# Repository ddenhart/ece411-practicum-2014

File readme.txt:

// ECE 411 - readme
// ddenhart@pdx.edu
// jerscott@pdx.edu
// ccarmen@pdx.edu
// nsl2@pdx.edu

---2014.10.05 nslj---
   - Initial readme added
   - Added Carmen's decision matrix to repo
   - Added Carmen's project proposals to repo
   - Added Jeremiah's project proposals to repo
   - Added Nick's project proposals to repo
   - Added Deb's project proposals to repo
   - Added personal scoring to decision matrix
  
---2014.10.05 dd---
   - Added personal scoring to decision matrix
   - updated readme 

---2014.10.06 ccarmen---
   - Added personal scoring to decision matrix
   - Added approx. cost for my proposals
   - updated readme 

---2014.10.06 jerscott---
   - Added scores and proposal costs to decision matrix
   - updated readme

---2014.10.08 nslj---
   - Added theoretical block diagram for belt project   

---2014.10.09 ccarmen---
   - Added meeting minutes on Wiki 
   - Added decision matrix 
 
---2014.10.11 dd---
   - Added color sensing proposals

---2014.10.11 jerscott---
   - Added power and vague proposals

---2014.10.11 nslj---
   - Added system overview block diagram
   - New stage folder created

---2014.10.11 ccarmen—--
   - Added LED options powerpoint

---2014.10.12 nslj---
   - Reorganized file folders to reflect latest updates (for observers)
   - Added the alternate proposals write up for HW2

---2014.10.12 jerscott---
   - Added updated Practicum Proposal

---2014.10.14 dd---
   -Added musts, shoulds and mays to the logbook wiki
   -Added datasheets & product links to the wiki
   -Filled out class forms with team members and project name
   -Added Microcontroller and Color Sensor datasheets and purchasing links to wiki
   -Added In-System Programmer links to wiki

---2014.10.14 ccarmen---
   - Added 10/11/2014 meeting minutes
   - Added RGB LED strip datasheet & product link to the wiki

---2014.10.16 ccarmen---
   - Added AVR programmer option links on Datasheet & Product Links page

---2014.10.18 ccarmen---
   - Added 10/18/2014 meeting minutes on the Wiki

---2014.10.18 dd---
   -Updated Wiki to have the T10 name and added summary
   -Added Project Proposal and Decision Matrix Pages
   -Made organized Wiki sidebar

---2014.10.19 cc---
   -Added LED output drawing to provide info for the project schematic

---2014.10.20 dd---
   - Added Color Sensor block drawing
   
---2014.10.21 cc---
   - Carmen Ciobanu implemented the new Weekly Progress Report format on the Wiki (individual and team combined)

---2014.10.22 dd---
   -Added the template pages for the individual weekly reports on the wiki
   -Filled in the past weekly reports

---2014.10.23 dd---
  - installed avr studio to start learning
  - installed winavr to start learning

---2014.10.23 jerscott---
   - Added PDS
   
---2014.10.24 dd---
   - Color sensors, Micontrollers, test RGB leds, power supply and ISP parts arrived

---2014.10.24 nslj---
   - Added schematic rough draft
   - Added brief write up on adding custom libraries to EAGLE

---2014.10.24 nslj---
  - Added meeting minues and updated WPR

---2014.10.27 jerscott---
   - Uploaded Revision 2 PDS

---2014.10.27 dd---
   - Sync'd readme and wpr's
   - breadboard power adapter component and last of other connectors arrived

---2014.10.29 nslj---
   - Added preliminary schematic for turn in
   - Updated wiki with schematic info
 
---2014.11.02 dd---
   - Sync'd readme and wpr's

---2014.11.5 nslj---
   - preliminary board layout uploaded
   - updated wiki with layout info

---2014.11.6 nslj---
   - completely rerouted board with correct size traces
   - redid components based on preliminary bill of materials
   - new switch, new capacitors!

---2014.11.06 jerscott---
   - Provided feedback for project schematic and board layout

---2014.11.07 cc---
   - Provided feedback for project schematic and board layout
   - Identified all the parts needed for our board on Digi-Key website and found new parts for the "package not available or not in stock" case
   - Created BOM with extra fields for manufacturer name, manufacturer part number, Digi-Key part number and direct links to components on Digi-Key website
   - Ordered all components on the BOM
   
---2014.11.08 dd---
   - made part names readable on the board 
   - project schedule proposal

---2014.11.08 cc—--
   - Received all board components from Digi-key
   - Printed board layout and put components on top
   - Good match 
   - Finished editing final version of BOM document

---2014.11.08 nslj---
   - final layout candidate uploaded!
     --fixed airwire @ (1.30,1.05)
     --smashed/sized some test points in Schematic
     --updated dimension layer of board for better spacing of mounting holes
     --added teamname info to both tPlace and tSilk layers
     --png screenshots of final layout candidate?

---2014.11.09 cc—--
   - Created Project Schedule document from project schedule documents provided by each team member
  
---2014.11.10 dd---
   - Reviewed and fitted the Project Schedule
   
---2014.11.15 dd---
   - Added the color sensor uml activity view

---2014.11.15 cc—--
   - Added LED Output driver protocol sequence diagram

---2014.11.16 nslj---
   - Added L0 system view block diagram
   - Added L1 system view block diagram
   - Added L0 module view for subcomponents in system view

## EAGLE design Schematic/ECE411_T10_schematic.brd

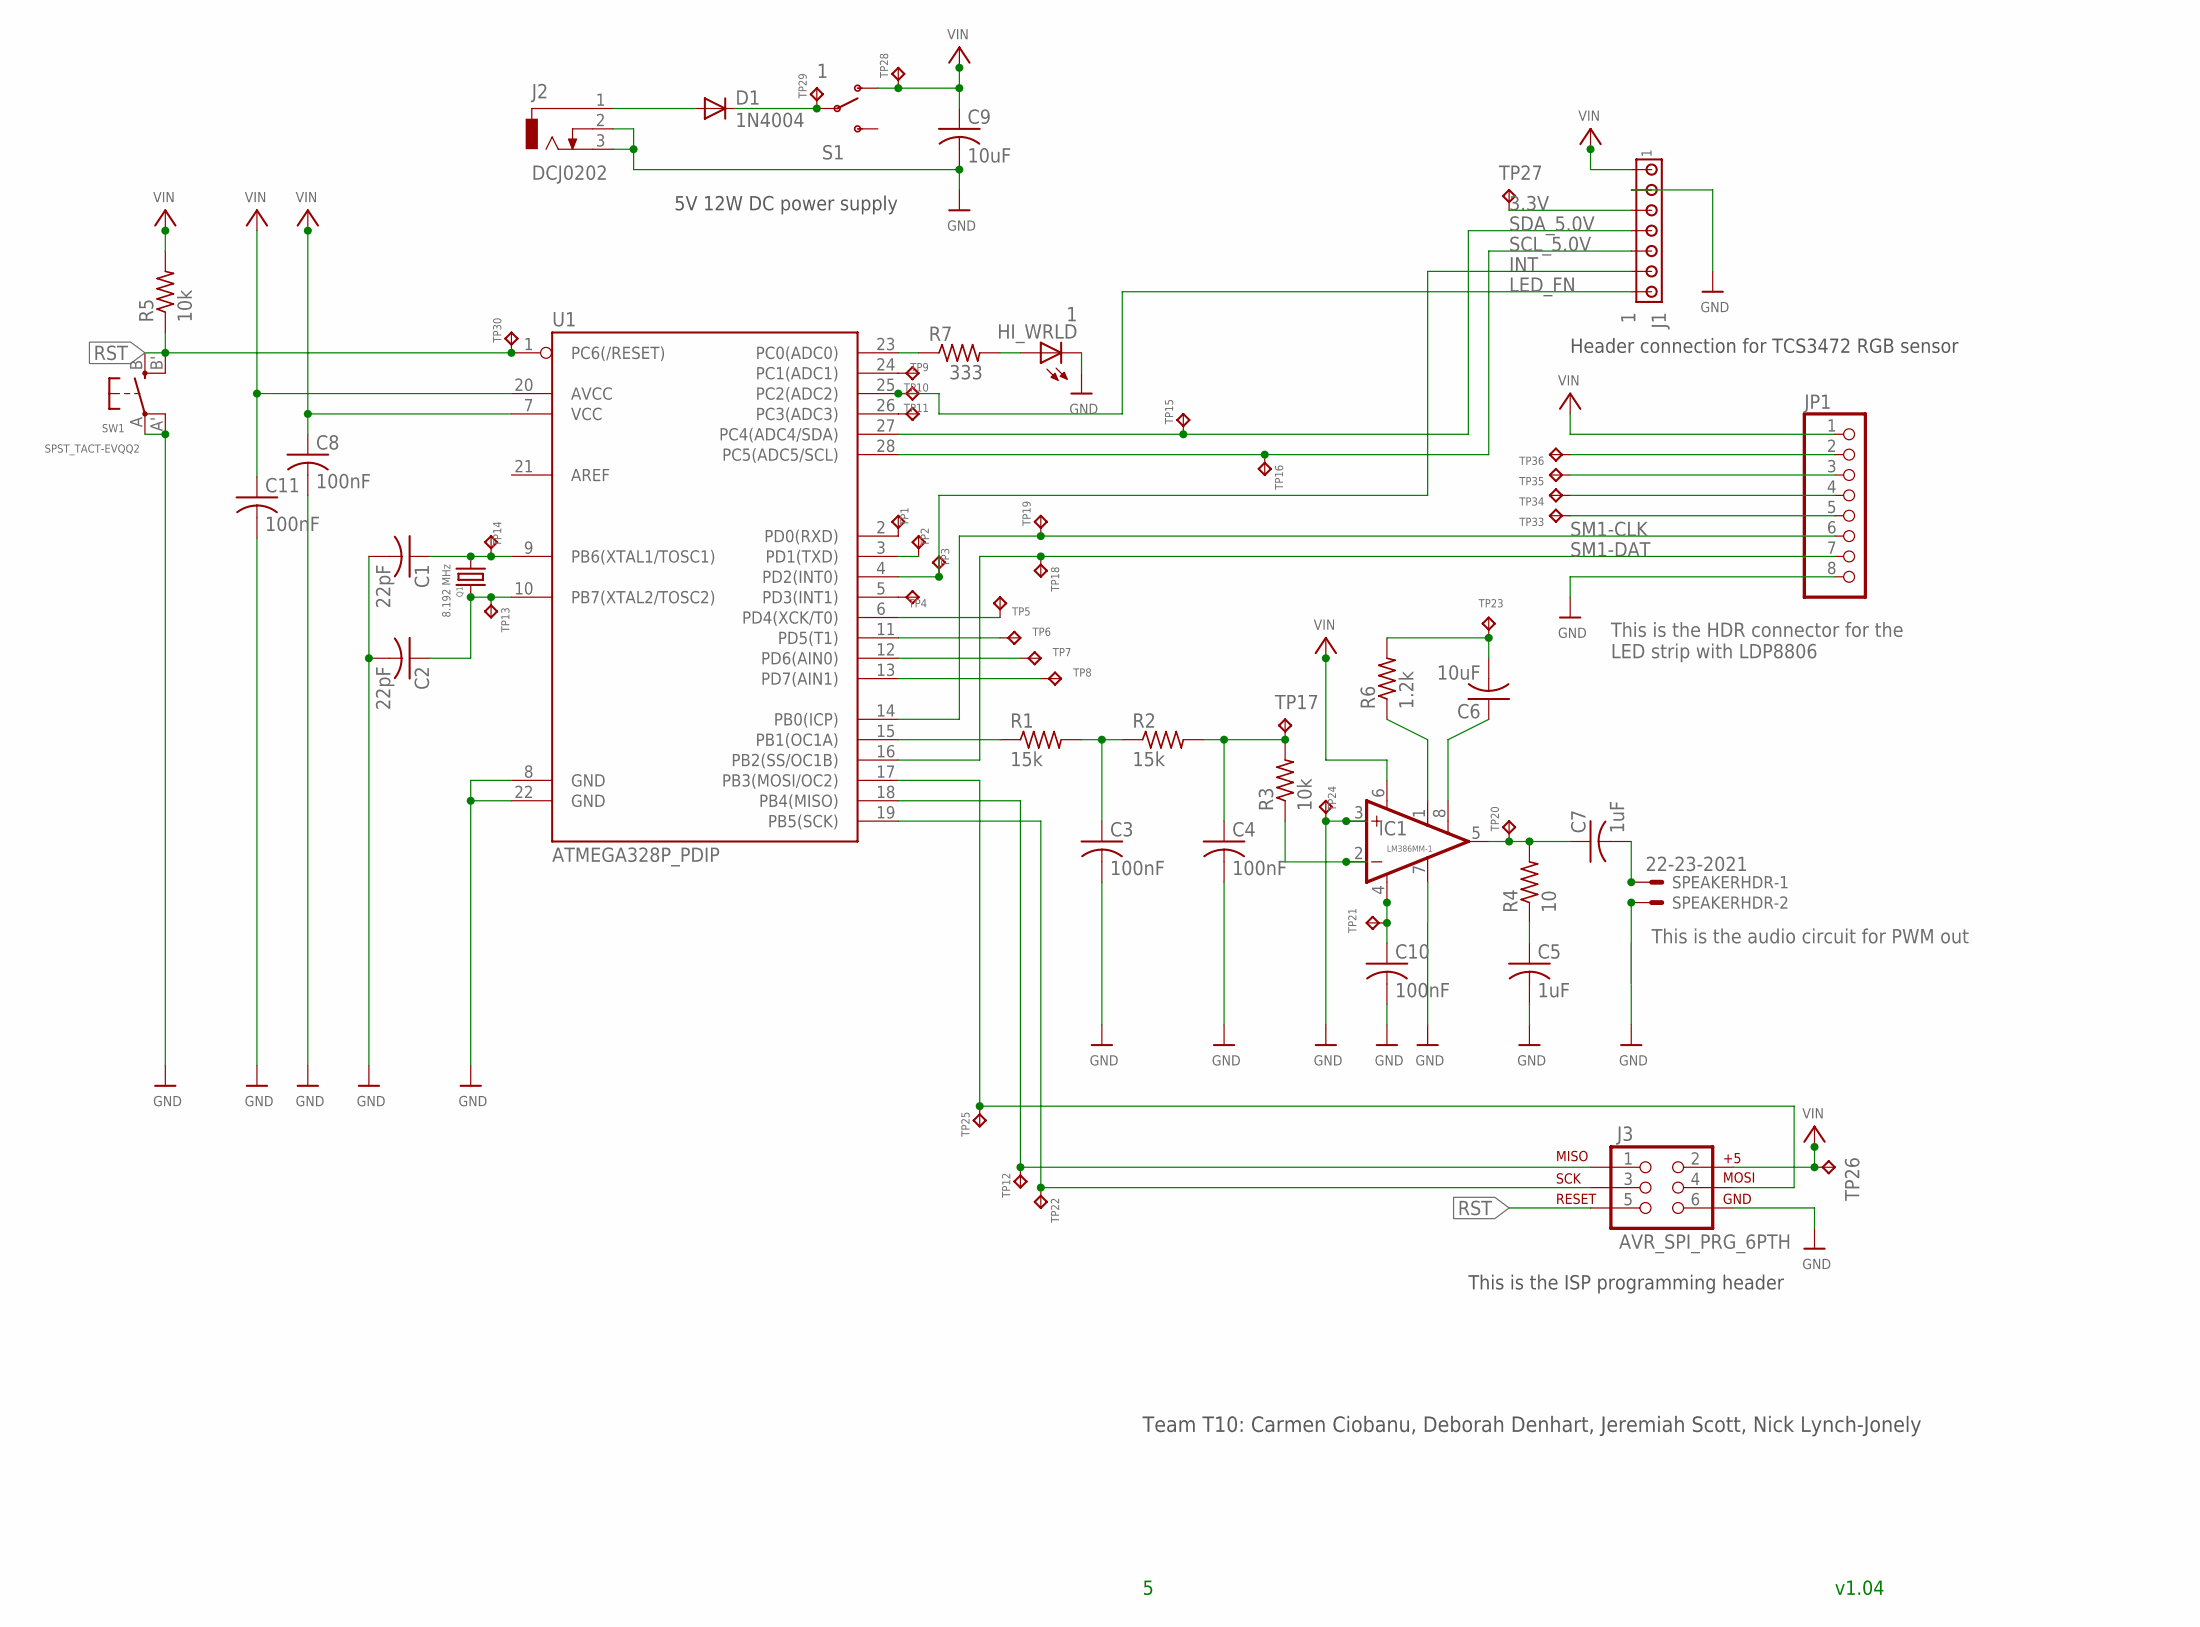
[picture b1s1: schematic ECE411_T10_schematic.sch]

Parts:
C1, C2: 22pF; C0805
C3, C4, C8, C10, C11: 100nF; C0805
C5, C7: 1uF; C0805
C6, C9: 10uF; C0805
D1: 1N4004; DO41-10
HI_WRLD: 1; SML1206
IC1: LM386MM-1; MMSOP08
J1: 1; 10X07MTA
J2: DCJ0202
J3: AVR_SPI_PRG_6PTH; 2X3
JP1: PINHD-1X8; 1X08
Q1: 8.192 MHz; HC49/S
R1, R2: 15k; M0805
R3, R5: 10k; M0805
R4: 10; M0805
R6: 1.2k; M0805
R7: 333; M0805
S1: 1; SWITCH-SPST-SMD-A
SPEAKERHDR: 22-23-2021
SW1: SPST_TACT-EVQQ2; EVQ-Q2
TP1, TP2, TP3, TP4, TP5, TP6, TP7, TP8, TP9, TP10, TP11, TP12, TP13, TP14, TP15, TP16, TP17, TP18, TP19, TP20, TP21, TP22, TP23, TP24, TP25, TP26, TP27, TP28, TP29, TP30, TP33, TP34, TP35, TP36: TPB1,27; B1,27
U1: ATMEGA328P_PDIP; DIL28-3

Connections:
3.3V: J1.3, TP27.TP
GND: C1.2, C2.2, C3.2, C4.2, C5.2, C8.2, C9.2, C10.2, C11.2, HI_WRLD.C, IC1.3 (+IN), IC1.7 (BYPASS), J1.2, J2.2, J2.3, J3.6, JP1.8, SPEAKERHDR.2, SW1.A, SW1.A' (P1), TP24.TP, U1.8 (GND), U1.22 (GND)
INT: J1.6, TP3.TP, U1.4 (PD2(INT0))
LED_FN: J1.7, TP10.TP, U1.25 (PC2(ADC2))
unnamed: C2.1, Q1.1, TP13.TP, U1.10 (PB7(XTAL2/TOSC2))
unnamed: C1.1, Q1.2, TP14.TP, U1.9 (PB6(XTAL1/TOSC1))
unnamed: IC1.1 (GAIN), R6.1
unnamed: R1.1, U1.15 (PB1(OC1A))
unnamed: C3.1, R1.2, R2.1
unnamed: C4.1, R2.2, R3.2, TP17.TP
unnamed: C6.1, IC1.8 (GAIN)
unnamed: IC1.2 (-IN), R3.1
unnamed: C5.1, R4.1
unnamed: R7.1, U1.23 (PC0(ADC0))
unnamed: C6.2, R6.2, TP23.TP
unnamed: C7.1, IC1.5 (OUT), R4.2, TP20.TP
unnamed: D1.A, J2.1
unnamed: C7.2, SPEAKERHDR.1
unnamed: D1.C, S1.2, TP29.TP
unnamed: TP1.TP, U1.2 (PD0(RXD))
unnamed: HI_WRLD.A, R7.2
unnamed: J3.3, TP22.TP, U1.19 (PB5(SCK))
unnamed: J3.1, TP12.TP, U1.18 (PB4(MISO))
unnamed: J3.4, TP25.TP, U1.17 (PB3(MOSI/OC2))
unnamed: TP5.TP, U1.6 (PD4(XCK/T0))
unnamed: TP2.TP, U1.3 (PD1(TXD))
unnamed: TP4.TP, U1.5 (PD3(INT1))
unnamed: TP6.TP, U1.11 (PD5(T1))
unnamed: TP7.TP, U1.12 (PD6(AIN0))
unnamed: TP8.TP, U1.13 (PD7(AIN1))
unnamed: TP9.TP, U1.24 (PC1(ADC1))
unnamed: TP11.TP, U1.26 (PC3(ADC3))
unnamed: C10.1, IC1.4 (GND), TP21.TP
unnamed: JP1.2, TP36.TP
unnamed: JP1.3, TP35.TP
unnamed: JP1.4, TP34.TP
unnamed: JP1.5, TP33.TP
RST: J3.5, R5.1, SW1.B (S), SW1.B' (S1), TP30.TP, U1.1 (PC6(/RESET))
SCL_5.0V: J1.5, TP16.TP, U1.28 (PC5(ADC5/SCL))
SDA_5.0V: J1.4, TP15.TP, U1.27 (PC4(ADC4/SDA))
SM1-CLK: JP1.6, TP19.TP, U1.14 (PB0(ICP))
SM1-DAT: JP1.7, TP18.TP, U1.16 (PB2(SS/OC1B))
VIN: C8.1, C9.1, C11.1, IC1.6 (VS), J1.1, J3.2, JP1.1, R5.2, S1.1 (O), TP26.TP, TP28.TP, U1.7 (VCC), U1.20 (AVCC)

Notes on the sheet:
This is the HDR connector for the LED strip with LDP8806
This is the audio circuit for PWM out
5V 12W DC power supply
Header connection for TCS3472 RGB sensor
Team T10: Carmen Ciobanu, Deborah Denhart, Jeremiah Scott, Nick Lynch-Jonely
v1.04
This is the ISP programming header

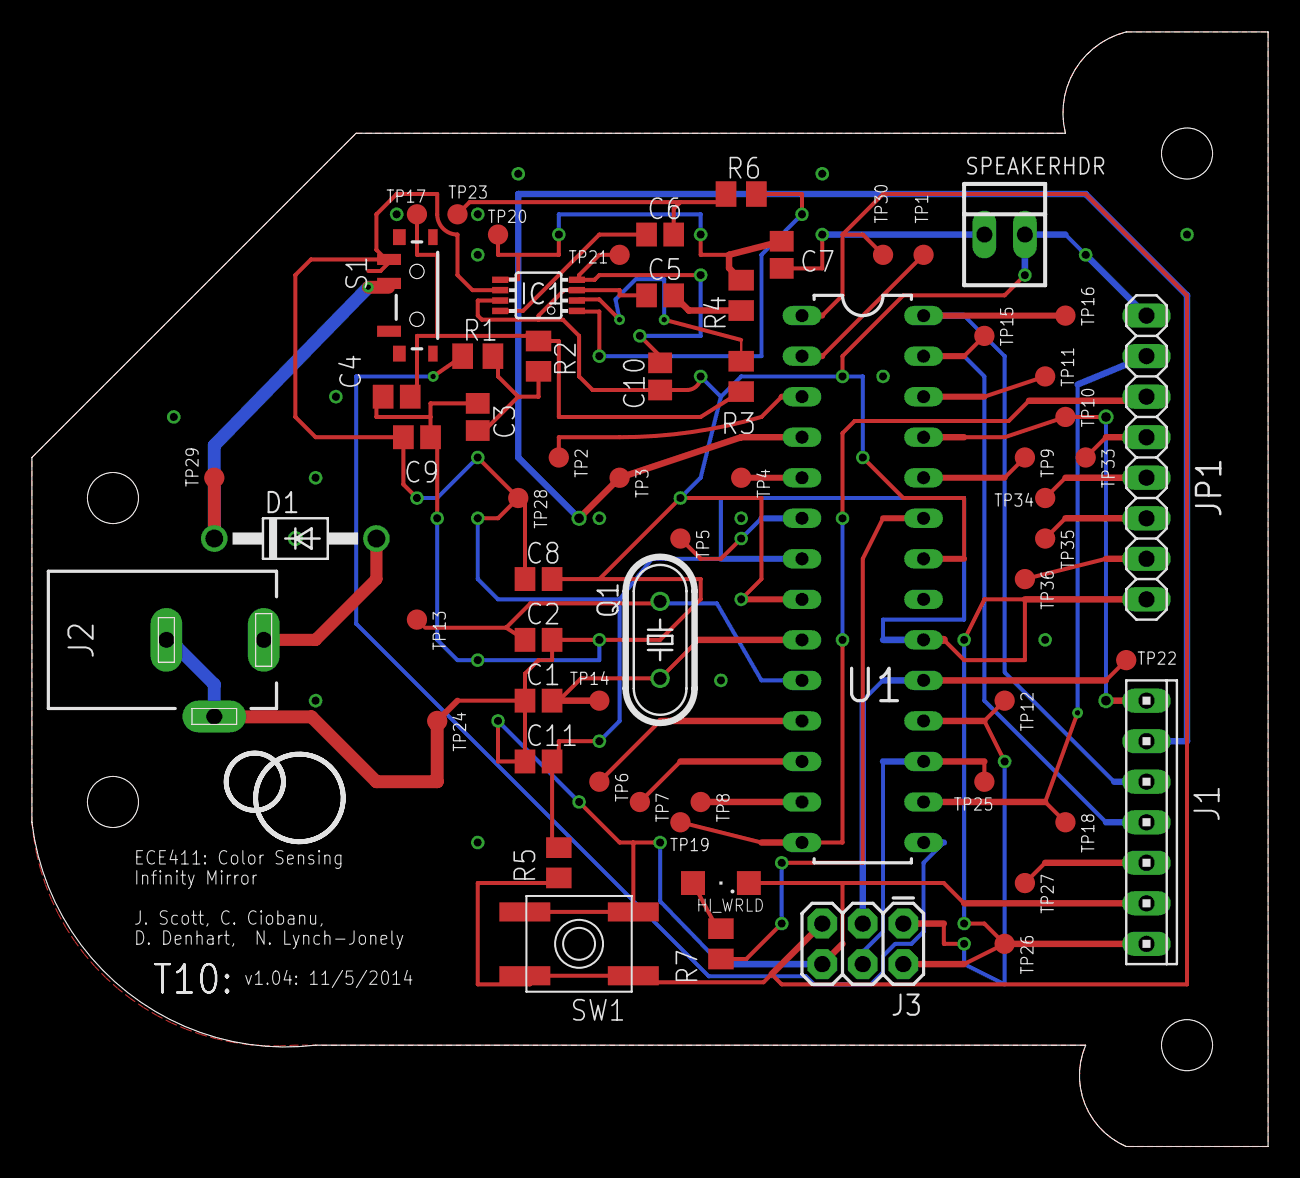
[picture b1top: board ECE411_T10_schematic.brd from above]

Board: 2 copper layers, 77.5 x 69.8 mm, 64 parts (0 on the bottom side), 43 nets.

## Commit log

2014-10-19 LED Output Drawing
    LED Output Drawing for preliminary schematic
2014-10-19 LED Output Photo
    LED Output Photo to reference in the Wiki
2014-10-20 Color Sensor diagram
2014-10-20 update folder
2014-10-23 PDS
    Adding Product Design Specifications
2014-10-24 added schematic
    t10_schem
2014-10-24 schematic.png
    terrible first draft, but the parts are there
2014-10-27 updated readme
    updated readme with meeting minutes
2014-10-27 Revised PDS
    Uploading revised PDS
2014-10-29 official preliminary schematic
    v1.01
2014-10-29 update readme
    readme updat for preliminary schematic
2014-10-29 ERC results
2014-10-29 prelim sch png
2014-10-29 readme update
2014-10-29 relabeled schematic name for turn in
    added issues text layer
2014-10-30 revisions
    some quick revisions and cleanup after lecture 10/29
2014-10-30 remove old schematic
2014-10-30 schematic: update pngs
2014-10-31 maybe logo?
2014-11-05 preliminary board layout
    very preliminary
2014-11-06 layout preliminary final
2014-11-06 reran DRC
    errors from vias.. what even happened to my ground plane. ugh.
2014-11-06 adding *.pn of prelim board layout
    prelim board layout
2014-11-07 Preliminary board 2: electric boogaloo
    completely rerouted the board with the correct size traces!
2014-11-07 new board layout screenshot
    *.png update of the new board
2014-11-08 made the board part names readable
2014-11-09 project schedule proposal
2014-11-09 Final BOM
    Final Bill of Materials document
2014-11-09 README updated
    README updated
2014-11-09 final layout candidate?
    - fixed airwire @ (1.30, 1.05)
    - smashed/sized some test points on Schematic
    - updated dimension layer of board layout for better spacing of mounting
    holes
    - added team name info to both tPlace and tSilk layers
    - png screenshots of final board layout candidate?
2014-11-09 readmeupdate
2014-11-09 schem_final png?
    final candidate for schematic
2014-11-09 more board edits - new pngs
    - moved test pad #14 as it was inaccessible
    - rerouted R6 R3 R4 for tKeepout
    - smash/resized some test points
    - updated pngs
2014-11-09 updated png
2014-11-09 update git ignores
2014-11-09 layout/schematic changes
    - rerouted INT to PD2
    - rerouted LED_FN to PC2
    - increased trace size around pad connections
2014-11-09 crisis averted
    updated pngs of layout/schematic changes
2014-11-09 DRC results
    no errors (except known ones in the tStop layer)
2014-11-09 OSHpark renders
    board is sent!
2014-11-10 Project Schedule
    Combined version of project schedule
2014-11-10 REDME update
    REDME update
2014-11-10 reviewed project schedule
2014-11-16 color sensor uml
2014-11-16 LED Output Driver protocol
    LED Output Driver protocol sequence diagram and updated BOM
2014-11-16 Updated README
    Updated README
2014-11-17 block diagrams
    HW5
2014-11-17 hw5
    hw5 compiled pdfs
2014-11-17 fixed landscap
    rescaled

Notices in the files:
parts and their libraries:
SparkFun-Connectors: Licensing: Creative Commons ShareAlike 4.0 International - https://creativecommons.org/licenses/by-sa/4.0
